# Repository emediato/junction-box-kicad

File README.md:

# junction_box_kicad
pcb with esp32

Hardware design knowledge .
1. While designing with ethernet 10/100/1000 speed we need to keep the following in mind as below.
2. Ethernet needs esd protection
3. RJ45 port will need EMI filters
4. Ethernet TX and RX pairs need to be impedance matched lines.
5. Shorter traces will provide better emi immunity.
6. We will need an Ethernet PHY interface chip
7. PHY data input lines need series resistors for reflection arrest.
8. Length Matched RX TX pair will improve the link quality and reliability.

https://www.st.com/resource/en/datasheet/l298.pdf

https://projects.raspberrypi.org/en/projects/physical-computing/14
https://www.hackster.io/officine/interfacing-arduino-mkr-or-esp-via-mqtt-node-red-101-4833bc
https://grafana.com/blog/2023/10/23/monitor-temperature-and-humidity-with-grafana-and-raspberry-pi/
https://www.makerhero.com/blog/sensor-dht11-com-node-red-e-raspberry-pi/
https://blog.voltaicsystems.com/solar-powered-lora-radio-barometric-pressure-and-altimeter-tutorial/
https://timchooblog.wordpress.com/2016/06/14/configuring-the-johnny-five-robotics-library-to-work-in-node-red/
https://iotdesignpro.com/projects/interface-arduino-with-node-red-to-send-sensor-data-on-webpage

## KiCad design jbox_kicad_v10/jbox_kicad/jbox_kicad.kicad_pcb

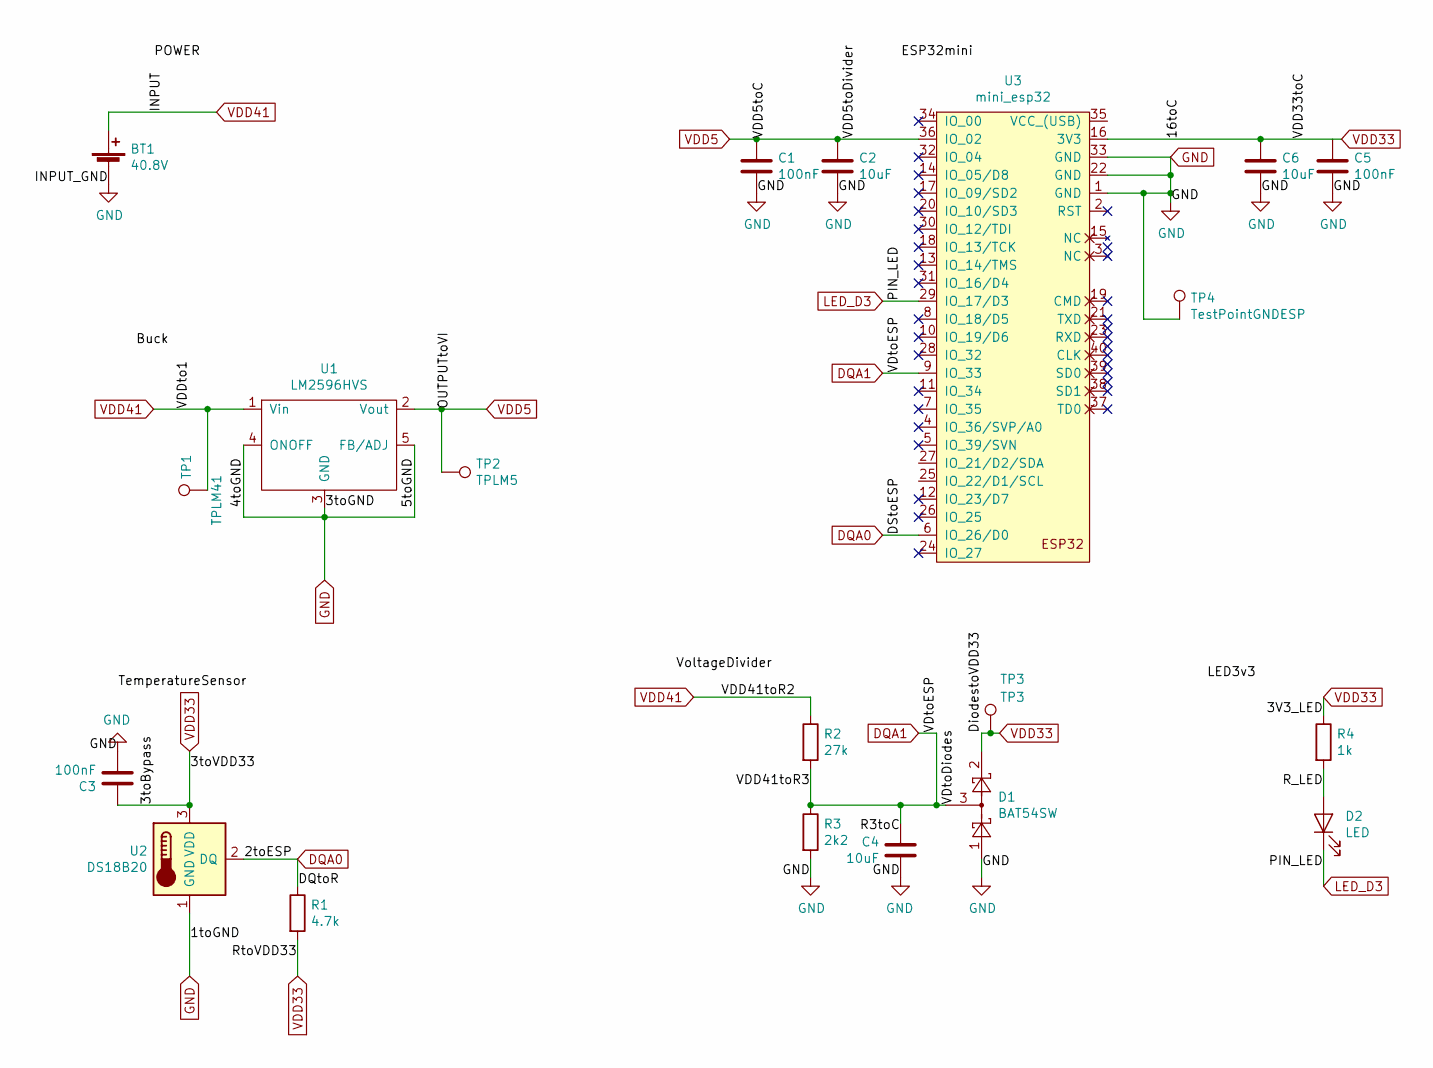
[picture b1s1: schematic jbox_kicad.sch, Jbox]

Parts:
BT1: 40.8V; Battery_Panasonic_CR1025-VSK_Vertical_CircularHoles
C1, C3, C5: 100nF; C_0805_2012Metric_Pad1.15x1.40mm_HandSolder
C2, C4, C6: 10uF; C_0805_2012Metric_Pad1.15x1.40mm_HandSolder
D1: BAT54SW; SOT-23-5_HandSoldering
D2: LED; LED_0805_2012Metric_Pad1.15x1.40mm_HandSolder
R1: 4.7k; R_0805_2012Metric_Pad1.15x1.40mm_HandSolder
R2: 27k; R_0805_2012Metric_Pad1.15x1.40mm_HandSolder
R3: 2k2; R_0805_2012Metric_Pad1.15x1.40mm_HandSolder
R4: 1k; R_0805_2012Metric_Pad1.15x1.40mm_HandSolder
TP1: TPLM41; TestPoint_Pad_1.0x1.0mm
TP2: TPLM5; TestPoint_Pad_1.0x1.0mm
TP3: TP3; TestPoint_Pad_1.0x1.0mm
TP4: TestPointGNDESP; TestPoint_Pad_D1.0mm
U1: LM2596HVS; TO-263-5_TabPin3
U2: DS18B20; TO-92_Inline
U3: mini_esp32; ESP32_mini

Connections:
/R_LED: D2.2 (A), R4.2
DQA0: R1.1, U2.2 (DQ), U3.6 (IO_26/D0)
DQA1: C4.1, D1.3, R2.2, R3.1, U3.9 (IO_33)
GND: BT1.2 (-), C1.2, C2.2, C3.2, C4.2, C5.2, C6.2, D1.1, R3.2, TP4.1, U1.3 (GND), U1.4 (ONOFF), U1.5 (FB/ADJ), U2.1 (GND), U3.1 (GND), U3.22 (GND), U3.33 (GND)
LED_D3: D2.1 (K), U3.29 (IO_17/D3)
VDD5: C1.1, C2.1, TP2.1, U1.2 (Vout), U3.36 (IO_02)
VDD33: C3.1, C5.1, C6.1, D1.2, R1.2, R4.1, TP3.1, U2.3 (VDD), U3.16 (3V3)
VDD41: BT1.1 (+), R2.1, TP1.1, U1.1 (Vin)

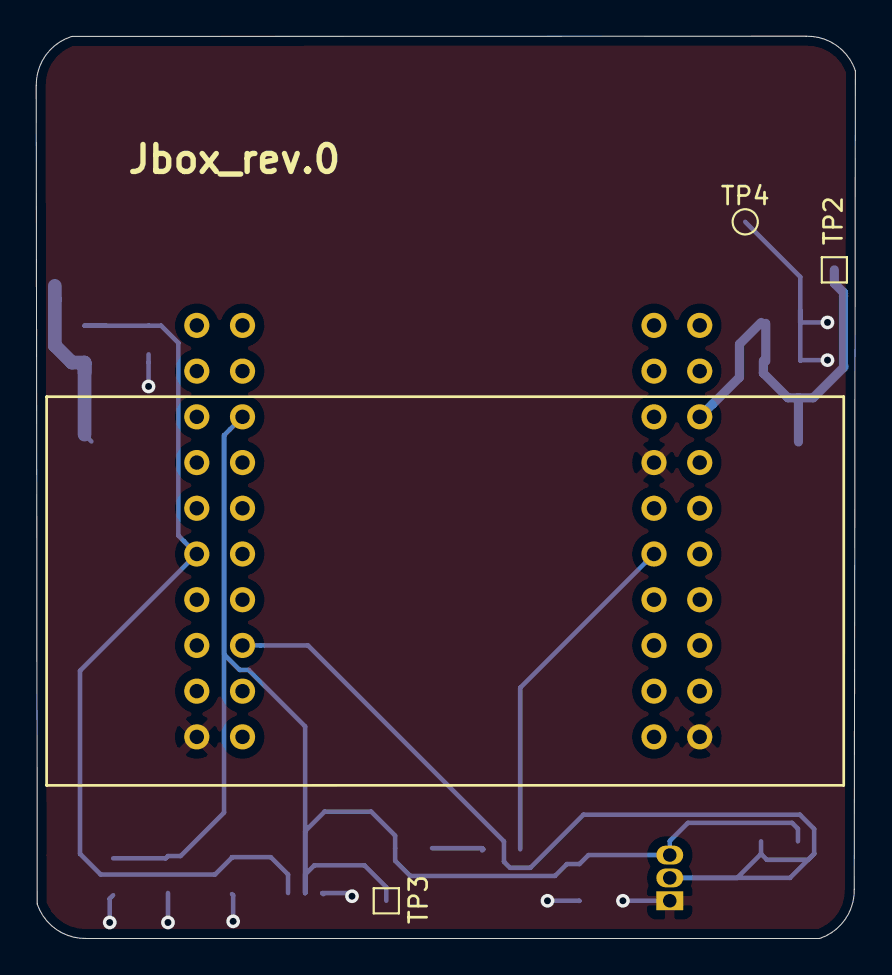
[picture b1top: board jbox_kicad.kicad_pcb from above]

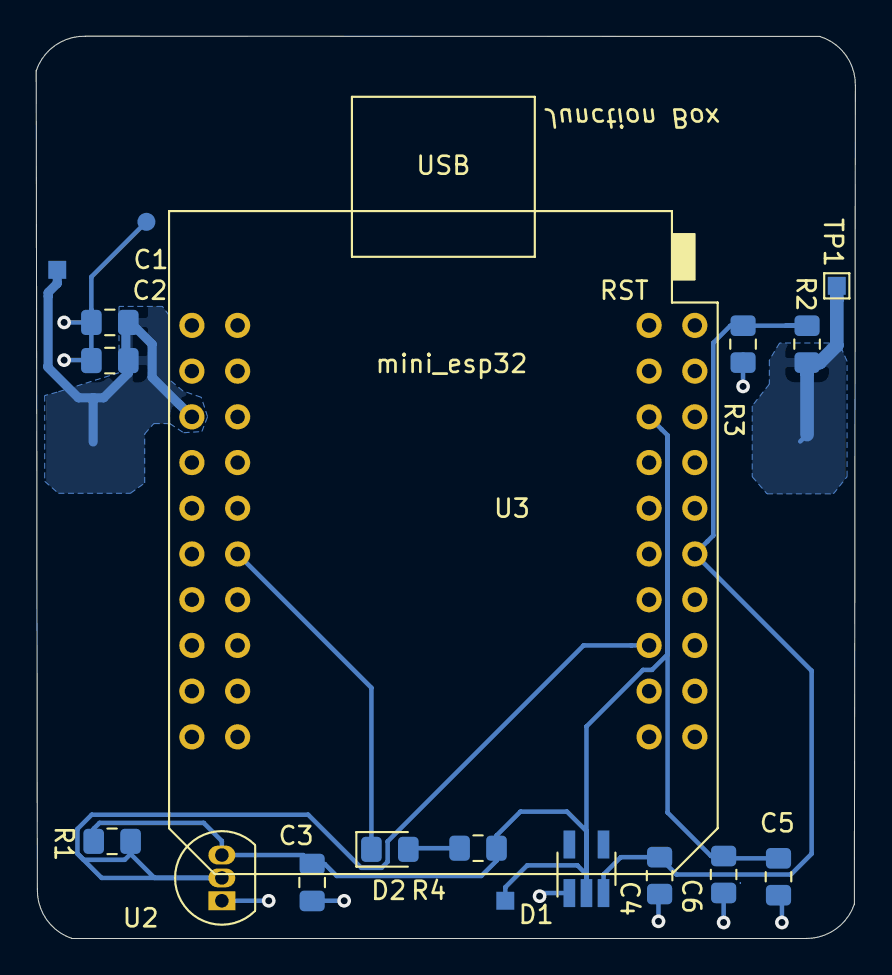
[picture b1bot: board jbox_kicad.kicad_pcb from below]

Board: 2 copper layers, 45.5 x 50.1 mm, 18 parts (15 on the bottom side), 8 nets.
